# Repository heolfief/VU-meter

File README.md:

# VU-meter

## Table of contents

- [Description](#description)
- [Hardware](#hardware)
- [Software](#software)
- [Copyright and license](#copyright-and-license)

## Description
This project is an AVR based LED VU-meter. It's display consists of 80 LEDs per audio channel. Each PCB holds all the LEDs, the analog and digital segments of the circuit and only handle one audio channel. That way you can build a stereo VU-meter just by using two instances of this circuit (which can be mechanically stacked together). Each audio channel will be completely separated and computed separately by the AVR microcontroller on each PCB.

### Pictures

## Hardware
The hardware is based on 3 main components:
- ATmega328p AVR microcontroller
- MCP6004 quad op-amp
- 74HC595 shift-registers for extended MCU outputs

This board runs on 5V DC power and should not exceed 500mA of current draw (All LEDs lit up).
A stabilized power supply is needed in order to provide clean power to the analog circuit.

### PCB
Populated PCB picture:

Bare PCB pictures:

The PCB was manufactured by <a target="_blank" href="https://www.pcbway.com">PCBWay</a>. Total cost was 44$ including shipping to France by DHL for 5 pieces.

I received the PCB 6 days after placing order on their website. General quality is good. Highly recommend their service.

### Documents available

- <a target="_blank" href="https://github.com/heolfief/VU-meter/blob/master/Hardware/Schematics.pdf">Schematics (PDF)</a>
- <a target="_blank" href="https://github.com/heolfief/VU-meter/blob/master/Hardware/BOM.pdf">Bill of materials (PDF)</a>
- <a target="_blank" href="https://github.com/heolfief/VU-meter/blob/master/Hardware/CAD/Eagle%20files">Autodesk Eagle CAD files</a>
- <a href="https://github.com/heolfief/VU-meter/tree/master/Hardware/CAD/GerberFiles">Gerber files</a>

## Software
The Firmware for the AVR microcontroller is written in C.

- IDE : Atmel Studio 7.0 (can be opened in MPLAB X)
- Compiler : avr-gcc

### Documents available

- <a target="_blank" href="https://heolfief.github.io/VU-meter/">Code documentation (doxygen)</a>

## Copyright and license
heolfief/VU-meter is licensed under the GNU General Public License v3.0.

See the <a target="_blank" href="https://github.com/heolfief/VU-meter/blob/master/LICENSE">LICENSE file</a> for more information.

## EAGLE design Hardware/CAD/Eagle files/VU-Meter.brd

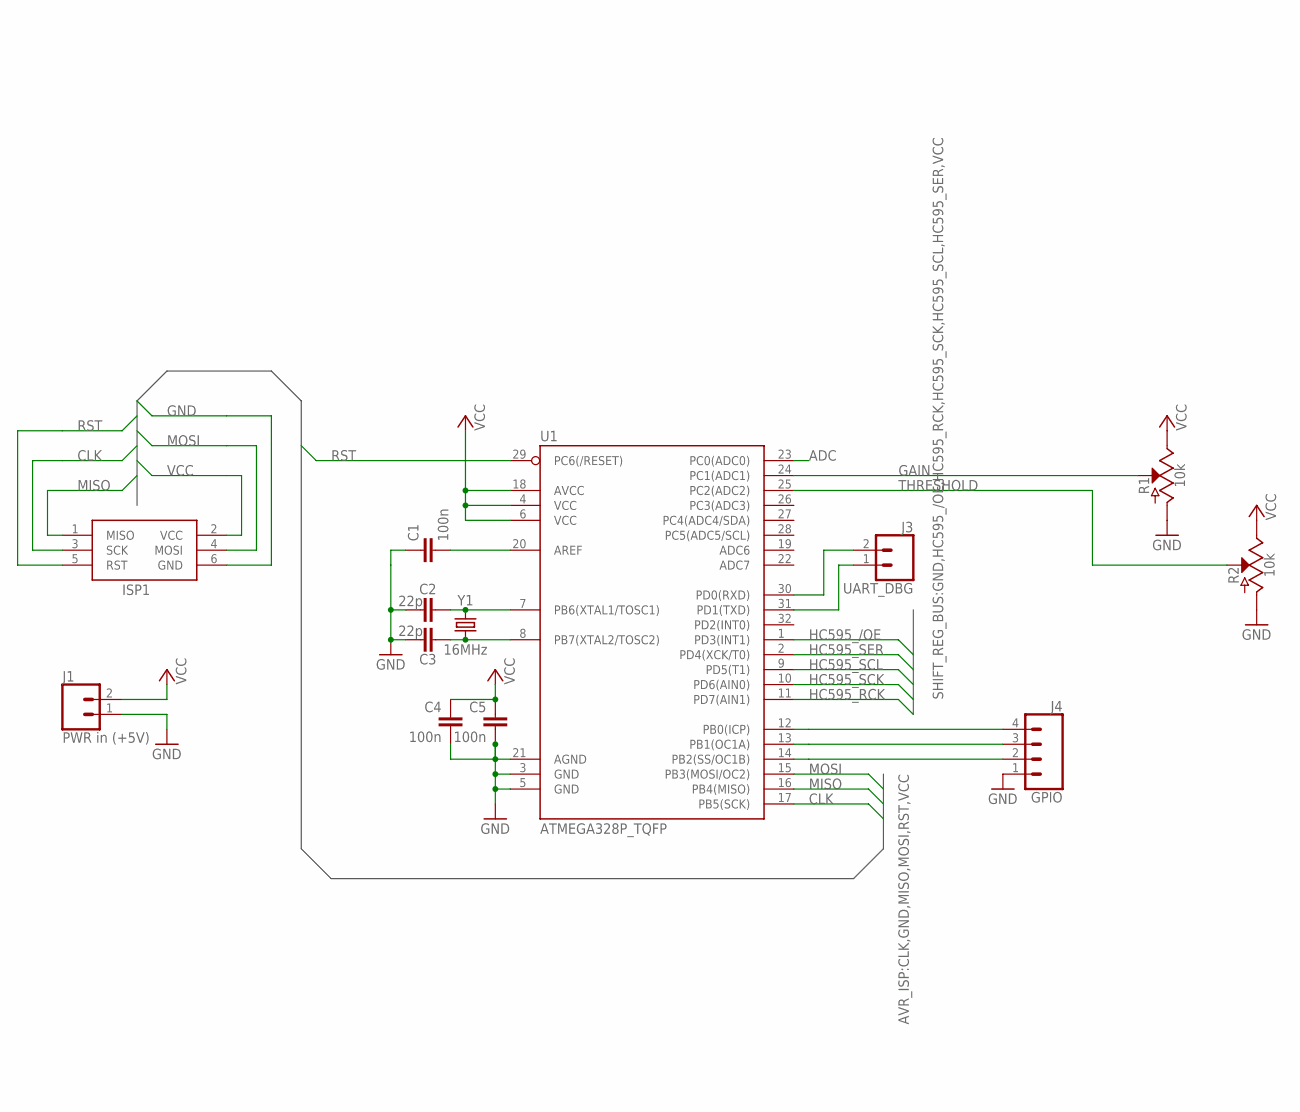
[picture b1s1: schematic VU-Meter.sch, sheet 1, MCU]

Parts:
C1, C4, C5: 100n; C0805
C2, C3: 22p; C0805
ISP1: AVRISP-6; AVRISP
J1: PWR in (+5V); 1X02
J3: UART_DBG; 1X02
J4: GPIO; 1X04
R1, R2: 10k; 1X03
U1: ATMEGA328P_TQFP; TQFP32-08
Y1: 16MHz; CRYSTAL-SMD-3.2X2.5MM

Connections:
ADC: U1.23 (PC0(ADC0)); also elsewhere on the board
CLK: ISP1.3 (SCK), U1.17 (PB5(SCK))
GAIN: R1.2 (S), U1.24 (PC1(ADC1))
GND: C1.1, C2.1, C3.1, C4.2, C5.2, ISP1.6 (GND), J1.1, J4.1, R1.3 (A), R2.3 (A), U1.3 (GND), U1.5 (GND), U1.21 (AGND); also elsewhere on the board
HC595_/OE: U1.1 (PD3(INT1)); also elsewhere on the board
HC595_RCK: U1.11 (PD7(AIN1)); also elsewhere on the board
HC595_SCK: U1.10 (PD6(AIN0)); also elsewhere on the board
HC595_SCL: U1.9 (PD5(T1)); also elsewhere on the board
HC595_SER: U1.2 (PD4(XCK/T0)); also elsewhere on the board
MISO: ISP1.1 (MISO), U1.16 (PB4(MISO))
MOSI: ISP1.4 (MOSI), U1.15 (PB3(MOSI/OC2))
unnamed: C1.2, U1.20 (AREF)
unnamed: C2.2, U1.7 (PB6(XTAL1/TOSC1)), Y1.3 (2)
unnamed: C3.2, U1.8 (PB7(XTAL2/TOSC2)), Y1.1
unnamed: J3.2, U1.30 (PD0(RXD))
unnamed: J3.1, U1.31 (PD1(TXD))
unnamed: J4.4, U1.12 (PB0(ICP))
unnamed: J4.3, U1.13 (PB1(OC1A))
unnamed: J4.2, U1.14 (PB2(SS/OC1B))
RST: ISP1.5 (RST), U1.29 (PC6(/RESET))
THRESHOLD: R2.2 (S), U1.25 (PC2(ADC2))
VCC: C4.1, C5.1, ISP1.2 (VCC), J1.2, R1.1 (E), R2.1 (E), U1.4 (VCC), U1.6 (VCC), U1.18 (AVCC); also elsewhere on the board

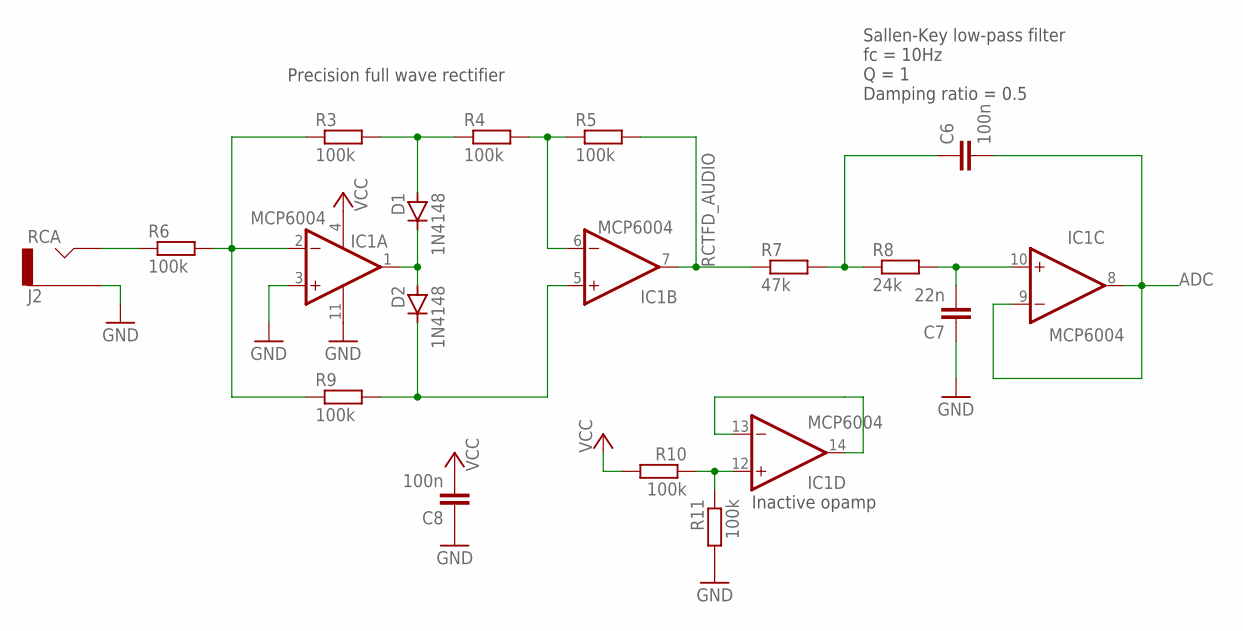
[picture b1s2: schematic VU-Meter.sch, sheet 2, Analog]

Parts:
C6, C8: 100n; C0805
C7: 22n; C0805
D1, D2: 1N4148; SOD80
IC1: MCP6004; SO14
J2: RCA; 1X02
R3, R4, R5, R6, R9, R10, R11: 100k; R0805
R7: 47k; R0805
R8: 24k; R0805

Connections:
ADC: C6.2, IC1.8 (OUT), IC1.9 (-IN); also elsewhere on the board
GND: C7.1, C8.1, IC1.3 (+IN), IC1.11 (V-), J2.2 (SLEEVE), R11.2; also elsewhere on the board
unnamed: IC1.2 (-IN), R3.1, R6.2, R9.1
unnamed: D2.1 (C), IC1.5 (+IN), R9.2
unnamed: D1.1 (C), D2.2 (A), IC1.1 (OUT)
unnamed: D1.2 (A), R3.2, R4.1
unnamed: IC1.6 (-IN), R4.2, R5.1
unnamed: J2.1 (TIP), R6.1
unnamed: C6.1, R7.2, R8.1
unnamed: C7.2, IC1.10 (+IN), R8.2
unnamed: IC1.13 (-IN), IC1.14 (OUT)
unnamed: IC1.12 (+IN), R10.1, R11.1
RCTFD_AUDIO: IC1.7 (OUT), R5.2, R7.1
VCC: C8.2, IC1.4 (V+), R10.2; also elsewhere on the board

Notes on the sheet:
Precision full wave rectifier
Sallen-Key low-pass filter fc = 10Hz Q = 1 Damping ratio = 0.5
Inactive opamp

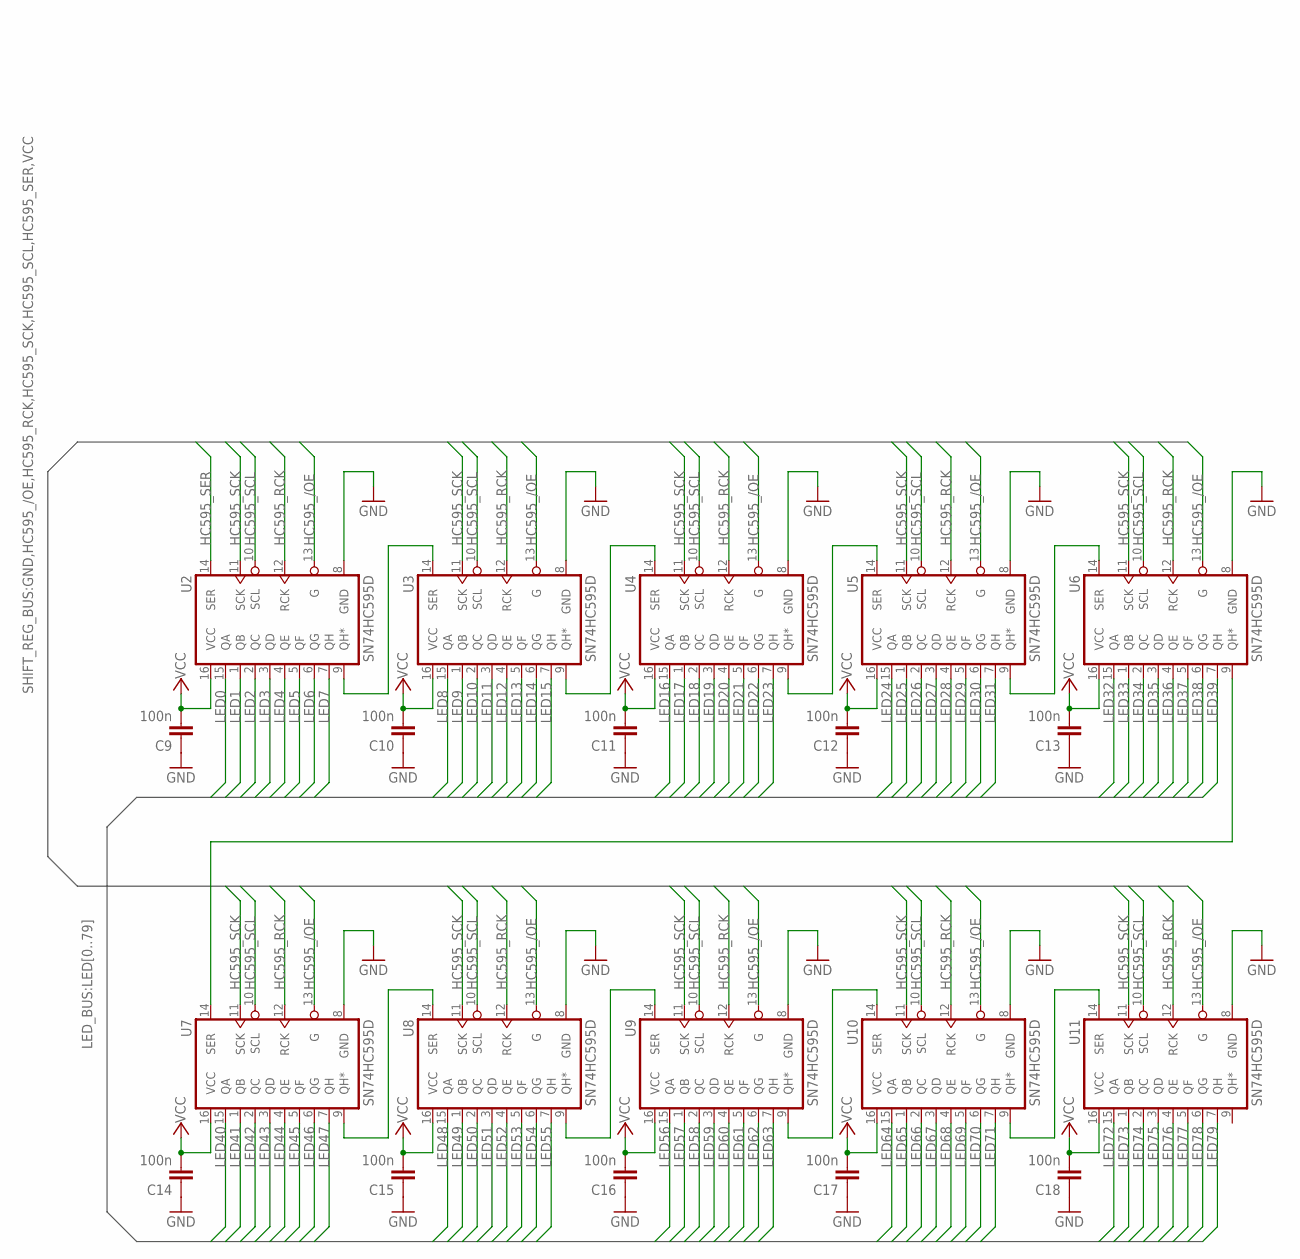
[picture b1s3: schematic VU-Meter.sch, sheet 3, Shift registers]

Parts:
C9, C10, C11, C12, C13, C14, C15, C16, C17, C18: 100n; C0805
U2, U3, U4, U5, U6, U7, U8, U9, U10, U11: SN74HC595D; SO16

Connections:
GND: C9.1, C10.1, C11.1, C12.1, C13.1, C14.1, C15.1, C16.1, C17.1, C18.1, U2.8 (GND), U3.8 (GND), U4.8 (GND), U5.8 (GND), U6.8 (GND), U7.8 (GND), U8.8 (GND), U9.8 (GND), U10.8 (GND), U11.8 (GND); also elsewhere on the board
HC595_/OE: U2.13 (G), U3.13 (G), U4.13 (G), U5.13 (G), U6.13 (G), U7.13 (G), U8.13 (G), U9.13 (G), U10.13 (G), U11.13 (G); also elsewhere on the board
HC595_RCK: U2.12 (RCK), U3.12 (RCK), U4.12 (RCK), U5.12 (RCK), U6.12 (RCK), U7.12 (RCK), U8.12 (RCK), U9.12 (RCK), U10.12 (RCK), U11.12 (RCK); also elsewhere on the board
HC595_SCK: U2.11 (SCK), U3.11 (SCK), U4.11 (SCK), U5.11 (SCK), U6.11 (SCK), U7.11 (SCK), U8.11 (SCK), U9.11 (SCK), U10.11 (SCK), U11.11 (SCK); also elsewhere on the board
HC595_SCL: U2.10 (SCL), U3.10 (SCL), U4.10 (SCL), U5.10 (SCL), U6.10 (SCL), U7.10 (SCL), U8.10 (SCL), U9.10 (SCL), U10.10 (SCL), U11.10 (SCL); also elsewhere on the board
HC595_SER: U2.14 (SER); also elsewhere on the board
LED0: U2.15 (QA); also elsewhere on the board
LED1: U2.1 (QB); also elsewhere on the board
LED2: U2.2 (QC); also elsewhere on the board
LED3: U2.3 (QD); also elsewhere on the board
LED4: U2.4 (QE); also elsewhere on the board
LED5: U2.5 (QF); also elsewhere on the board
LED6: U2.6 (QG); also elsewhere on the board
LED7: U2.7 (QH); also elsewhere on the board
LED8: U3.15 (QA); also elsewhere on the board
LED9: U3.1 (QB); also elsewhere on the board
LED10: U3.2 (QC); also elsewhere on the board
LED11: U3.3 (QD); also elsewhere on the board
LED12: U3.4 (QE); also elsewhere on the board
LED13: U3.5 (QF); also elsewhere on the board
LED14: U3.6 (QG); also elsewhere on the board
LED15: U3.7 (QH); also elsewhere on the board
LED16: U4.15 (QA); also elsewhere on the board
LED17: U4.1 (QB); also elsewhere on the board
LED18: U4.2 (QC); also elsewhere on the board
LED19: U4.3 (QD); also elsewhere on the board
LED20: U4.4 (QE); also elsewhere on the board
LED21: U4.5 (QF); also elsewhere on the board
LED22: U4.6 (QG); also elsewhere on the board
LED23: U4.7 (QH); also elsewhere on the board
LED24: U5.15 (QA); also elsewhere on the board
LED25: U5.1 (QB); also elsewhere on the board
LED26: U5.2 (QC); also elsewhere on the board
LED27: U5.3 (QD); also elsewhere on the board
LED28: U5.4 (QE); also elsewhere on the board
LED29: U5.5 (QF); also elsewhere on the board
LED30: U5.6 (QG); also elsewhere on the board
LED31: U5.7 (QH); also elsewhere on the board
LED32: U6.15 (QA); also elsewhere on the board
LED33: U6.1 (QB); also elsewhere on the board
LED34: U6.2 (QC); also elsewhere on the board
LED35: U6.3 (QD); also elsewhere on the board
LED36: U6.4 (QE); also elsewhere on the board
LED37: U6.5 (QF); also elsewhere on the board
LED38: U6.6 (QG); also elsewhere on the board
LED39: U6.7 (QH); also elsewhere on the board
LED40: U7.15 (QA); also elsewhere on the board
LED41: U7.1 (QB); also elsewhere on the board
LED42: U7.2 (QC); also elsewhere on the board
LED43: U7.3 (QD); also elsewhere on the board
LED44: U7.4 (QE); also elsewhere on the board
LED45: U7.5 (QF); also elsewhere on the board
LED46: U7.6 (QG); also elsewhere on the board
LED47: U7.7 (QH); also elsewhere on the board
LED48: U8.15 (QA); also elsewhere on the board
LED49: U8.1 (QB); also elsewhere on the board
LED50: U8.2 (QC); also elsewhere on the board
LED51: U8.3 (QD); also elsewhere on the board
LED52: U8.4 (QE); also elsewhere on the board
LED53: U8.5 (QF); also elsewhere on the board
LED54: U8.6 (QG); also elsewhere on the board
LED55: U8.7 (QH); also elsewhere on the board
LED56: U9.15 (QA); also elsewhere on the board
LED57: U9.1 (QB); also elsewhere on the board
LED58: U9.2 (QC); also elsewhere on the board
LED59: U9.3 (QD); also elsewhere on the board
LED60: U9.4 (QE); also elsewhere on the board
LED61: U9.5 (QF); also elsewhere on the board
LED62: U9.6 (QG); also elsewhere on the board
LED63: U9.7 (QH); also elsewhere on the board
LED64: U10.15 (QA); also elsewhere on the board
LED65: U10.1 (QB); also elsewhere on the board
LED66: U10.2 (QC); also elsewhere on the board
LED67: U10.3 (QD); also elsewhere on the board
LED68: U10.4 (QE); also elsewhere on the board
LED69: U10.5 (QF); also elsewhere on the board
LED70: U10.6 (QG); also elsewhere on the board
LED71: U10.7 (QH); also elsewhere on the board
LED72: U11.15 (QA); also elsewhere on the board
LED73: U11.1 (QB); also elsewhere on the board
LED74: U11.2 (QC); also elsewhere on the board
LED75: U11.3 (QD); also elsewhere on the board
LED76: U11.4 (QE); also elsewhere on the board
LED77: U11.5 (QF); also elsewhere on the board
LED78: U11.6 (QG); also elsewhere on the board
LED79: U11.7 (QH); also elsewhere on the board
unnamed: U2.9 (QH*), U3.14 (SER)
unnamed: U3.9 (QH*), U4.14 (SER)
unnamed: U4.9 (QH*), U5.14 (SER)
unnamed: U5.9 (QH*), U6.14 (SER)
unnamed: U7.9 (QH*), U8.14 (SER)
unnamed: U8.9 (QH*), U9.14 (SER)
unnamed: U9.9 (QH*), U10.14 (SER)
unnamed: U10.9 (QH*), U11.14 (SER)
unnamed: U6.9 (QH*), U7.14 (SER)
VCC: C9.2, C10.2, C11.2, C12.2, C13.2, C14.2, C15.2, C16.2, C17.2, C18.2, U2.16 (VCC), U3.16 (VCC), U4.16 (VCC), U5.16 (VCC), U6.16 (VCC), U7.16 (VCC), U8.16 (VCC), U9.16 (VCC), U10.16 (VCC), U11.16 (VCC); also elsewhere on the board

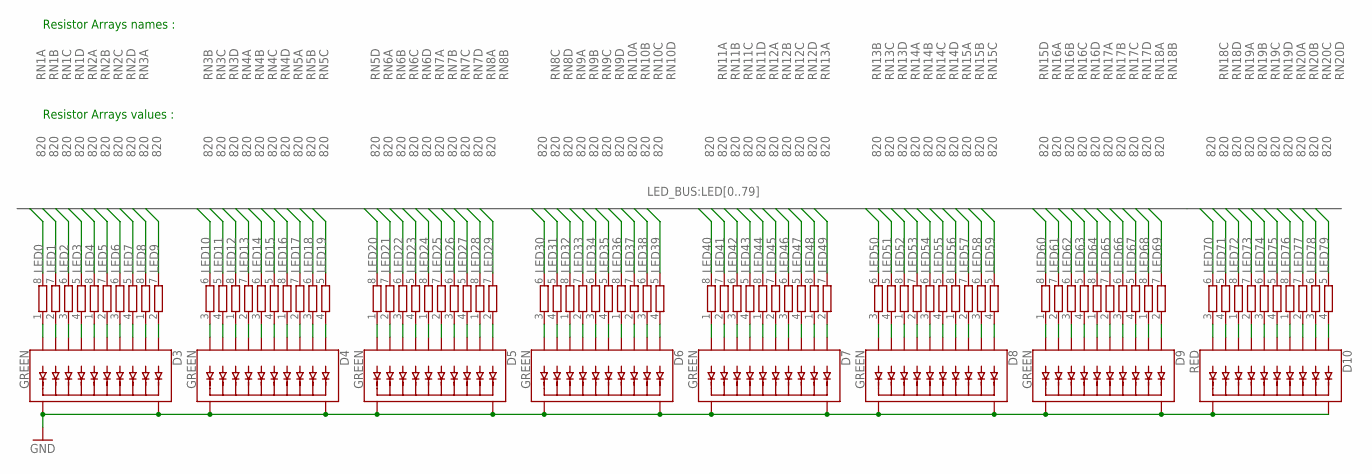
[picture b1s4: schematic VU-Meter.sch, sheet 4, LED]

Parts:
D3, D4, D5, D6, D7, D8, D9: GREEN; LED_BARGRAPH_OFFBOARD_RIGHT_ANGLE
D10: RED; LED_BARGRAPH_OFFBOARD_RIGHT_ANGLE
RN1, RN2, RN3, RN4, RN5, RN6, RN7, RN8, RN9, RN10, RN11, RN12, RN13, RN14, RN15, RN16, RN17, RN18, RN19, RN20: 820; 0603-ARC

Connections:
GND: D3.P$11 (C), D3.P$12 (C1), D4.P$11 (C), D4.P$12 (C1), D5.P$11 (C), D5.P$12 (C1), D6.P$11 (C), D6.P$12 (C1), D7.P$11 (C), D7.P$12 (C1), D8.P$11 (C), D8.P$12 (C1), D9.P$11 (C), D9.P$12 (C1), D10.P$11 (C), D10.P$12 (C1); also elsewhere on the board
LED0: RN1.8 (2); also elsewhere on the board
LED1: RN1.7 (2); also elsewhere on the board
LED2: RN1.6 (2); also elsewhere on the board
LED3: RN1.5 (2); also elsewhere on the board
LED4: RN2.8 (2); also elsewhere on the board
LED5: RN2.7 (2); also elsewhere on the board
LED6: RN2.6 (2); also elsewhere on the board
LED7: RN2.5 (2); also elsewhere on the board
LED8: RN3.8 (2); also elsewhere on the board
LED9: RN3.7 (2); also elsewhere on the board
LED10: RN3.6 (2); also elsewhere on the board
LED11: RN3.5 (2); also elsewhere on the board
LED12: RN4.8 (2); also elsewhere on the board
LED13: RN4.7 (2); also elsewhere on the board
LED14: RN4.6 (2); also elsewhere on the board
LED15: RN4.5 (2); also elsewhere on the board
LED16: RN5.8 (2); also elsewhere on the board
LED17: RN5.7 (2); also elsewhere on the board
LED18: RN5.6 (2); also elsewhere on the board
LED19: RN5.5 (2); also elsewhere on the board
LED20: RN6.8 (2); also elsewhere on the board
LED21: RN6.7 (2); also elsewhere on the board
LED22: RN6.6 (2); also elsewhere on the board
LED23: RN6.5 (2); also elsewhere on the board
LED24: RN7.8 (2); also elsewhere on the board
LED25: RN7.7 (2); also elsewhere on the board
LED26: RN7.6 (2); also elsewhere on the board
LED27: RN7.5 (2); also elsewhere on the board
LED28: RN8.8 (2); also elsewhere on the board
LED29: RN8.7 (2); also elsewhere on the board
LED30: RN8.6 (2); also elsewhere on the board
LED31: RN8.5 (2); also elsewhere on the board
LED32: RN9.8 (2); also elsewhere on the board
LED33: RN9.7 (2); also elsewhere on the board
LED34: RN9.6 (2); also elsewhere on the board
LED35: RN9.5 (2); also elsewhere on the board
LED36: RN10.8 (2); also elsewhere on the board
LED37: RN10.7 (2); also elsewhere on the board
LED38: RN10.6 (2); also elsewhere on the board
LED39: RN10.5 (2); also elsewhere on the board
LED40: RN11.8 (2); also elsewhere on the board
LED41: RN11.7 (2); also elsewhere on the board
LED42: RN11.6 (2); also elsewhere on the board
LED43: RN11.5 (2); also elsewhere on the board
LED44: RN12.8 (2); also elsewhere on the board
LED45: RN12.7 (2); also elsewhere on the board
LED46: RN12.6 (2); also elsewhere on the board
LED47: RN12.5 (2); also elsewhere on the board
LED48: RN13.8 (2); also elsewhere on the board
LED49: RN13.7 (2); also elsewhere on the board
LED50: RN13.6 (2); also elsewhere on the board
LED51: RN13.5 (2); also elsewhere on the board
LED52: RN14.8 (2); also elsewhere on the board
LED53: RN14.7 (2); also elsewhere on the board
LED54: RN14.6 (2); also elsewhere on the board
LED55: RN14.5 (2); also elsewhere on the board
LED56: RN15.8 (2); also elsewhere on the board
LED57: RN15.7 (2); also elsewhere on the board
LED58: RN15.6 (2); also elsewhere on the board
LED59: RN15.5 (2); also elsewhere on the board
LED60: RN16.8 (2); also elsewhere on the board
LED61: RN16.7 (2); also elsewhere on the board
LED62: RN16.6 (2); also elsewhere on the board
LED63: RN16.5 (2); also elsewhere on the board
LED64: RN17.8 (2); also elsewhere on the board
LED65: RN17.7 (2); also elsewhere on the board
LED66: RN17.6 (2); also elsewhere on the board
LED67: RN17.5 (2); also elsewhere on the board
LED68: RN18.8 (2); also elsewhere on the board
LED69: RN18.7 (2); also elsewhere on the board
LED70: RN18.6 (2); also elsewhere on the board
LED71: RN18.5 (2); also elsewhere on the board
LED72: RN19.8 (2); also elsewhere on the board
LED73: RN19.7 (2); also elsewhere on the board
LED74: RN19.6 (2); also elsewhere on the board
LED75: RN19.5 (2); also elsewhere on the board
LED76: RN20.8 (2); also elsewhere on the board
LED77: RN20.7 (2); also elsewhere on the board
LED78: RN20.6 (2); also elsewhere on the board
LED79: RN20.5 (2); also elsewhere on the board
unnamed: D3.P$1 (A9), RN1.1
unnamed: D3.P$2 (A8), RN1.2 (1)
unnamed: D3.P$3 (A7), RN1.3 (1)
unnamed: D3.P$4 (A6), RN1.4 (1)
unnamed: D3.P$5 (A5), RN2.1
unnamed: D3.P$6 (A4), RN2.2 (1)
unnamed: D3.P$7 (A3), RN2.3 (1)
unnamed: D3.P$8 (A2), RN2.4 (1)
unnamed: D3.P$9 (A1), RN3.1
unnamed: D3.P$10 (A), RN3.2 (1)
unnamed: D4.P$1 (A9), RN3.3 (1)
unnamed: D4.P$2 (A8), RN3.4 (1)
unnamed: D4.P$3 (A7), RN4.1
unnamed: D4.P$4 (A6), RN4.2 (1)
unnamed: D4.P$5 (A5), RN4.3 (1)
unnamed: D4.P$6 (A4), RN4.4 (1)
unnamed: D4.P$7 (A3), RN5.1
unnamed: D4.P$8 (A2), RN5.2 (1)
unnamed: D4.P$9 (A1), RN5.3 (1)
unnamed: D4.P$10 (A), RN5.4 (1)
unnamed: D5.P$1 (A9), RN6.1
unnamed: D5.P$2 (A8), RN6.2 (1)
unnamed: D5.P$3 (A7), RN6.3 (1)
unnamed: D5.P$4 (A6), RN6.4 (1)
unnamed: D5.P$5 (A5), RN7.1
unnamed: D5.P$6 (A4), RN7.2 (1)
unnamed: D5.P$7 (A3), RN7.3 (1)
unnamed: D5.P$8 (A2), RN7.4 (1)
unnamed: D5.P$9 (A1), RN8.1
unnamed: D5.P$10 (A), RN8.2 (1)
unnamed: D6.P$1 (A9), RN8.3 (1)
unnamed: D6.P$2 (A8), RN8.4 (1)
unnamed: D6.P$3 (A7), RN9.1
unnamed: D6.P$4 (A6), RN9.2 (1)
unnamed: D6.P$5 (A5), RN9.3 (1)
unnamed: D6.P$6 (A4), RN9.4 (1)
unnamed: D6.P$7 (A3), RN10.1
unnamed: D6.P$8 (A2), RN10.2 (1)
unnamed: D6.P$9 (A1), RN10.3 (1)
unnamed: D6.P$10 (A), RN10.4 (1)
unnamed: D7.P$1 (A9), RN11.1
unnamed: D7.P$2 (A8), RN11.2 (1)
unnamed: D7.P$3 (A7), RN11.3 (1)
unnamed: D7.P$4 (A6), RN11.4 (1)
unnamed: D7.P$5 (A5), RN12.1
unnamed: D7.P$6 (A4), RN12.2 (1)
unnamed: D7.P$7 (A3), RN12.3 (1)
unnamed: D7.P$8 (A2), RN12.4 (1)
unnamed: D7.P$9 (A1), RN13.1
unnamed: D7.P$10 (A), RN13.2 (1)
unnamed: D8.P$1 (A9), RN13.3 (1)
unnamed: D8.P$2 (A8), RN13.4 (1)
unnamed: D8.P$3 (A7), RN14.1
unnamed: D8.P$4 (A6), RN14.2 (1)
unnamed: D8.P$5 (A5), RN14.3 (1)
unnamed: D8.P$6 (A4), RN14.4 (1)
unnamed: D8.P$7 (A3), RN15.1
unnamed: D8.P$8 (A2), RN15.2 (1)
unnamed: D8.P$9 (A1), RN15.3 (1)
unnamed: D8.P$10 (A), RN15.4 (1)
unnamed: D9.P$1 (A9), RN16.1
unnamed: D9.P$2 (A8), RN16.2 (1)
unnamed: D9.P$3 (A7), RN16.3 (1)
unnamed: D9.P$4 (A6), RN16.4 (1)
unnamed: D9.P$5 (A5), RN17.1
unnamed: D9.P$6 (A4), RN17.2 (1)
unnamed: D9.P$7 (A3), RN17.3 (1)
unnamed: D9.P$8 (A2), RN17.4 (1)
unnamed: D9.P$9 (A1), RN18.1
unnamed: D9.P$10 (A), RN18.2 (1)
unnamed: D10.P$1 (A9), RN18.3 (1)
unnamed: D10.P$2 (A8), RN18.4 (1)
unnamed: D10.P$3 (A7), RN19.1
unnamed: D10.P$4 (A6), RN19.2 (1)
unnamed: D10.P$5 (A5), RN19.3 (1)
unnamed: D10.P$6 (A4), RN19.4 (1)
unnamed: D10.P$7 (A3), RN20.1
unnamed: D10.P$8 (A2), RN20.2 (1)
unnamed: D10.P$9 (A1), RN20.3 (1)
unnamed: D10.P$10 (A), RN20.4 (1)

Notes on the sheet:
Resistor Arrays names :
Resistor Arrays values :

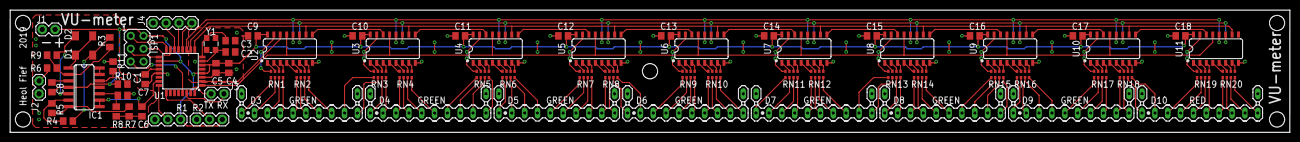
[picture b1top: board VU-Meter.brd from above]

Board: 2 copper layers, 252.7 x 24.1 mm, 77 parts (0 on the bottom side), 202 nets.

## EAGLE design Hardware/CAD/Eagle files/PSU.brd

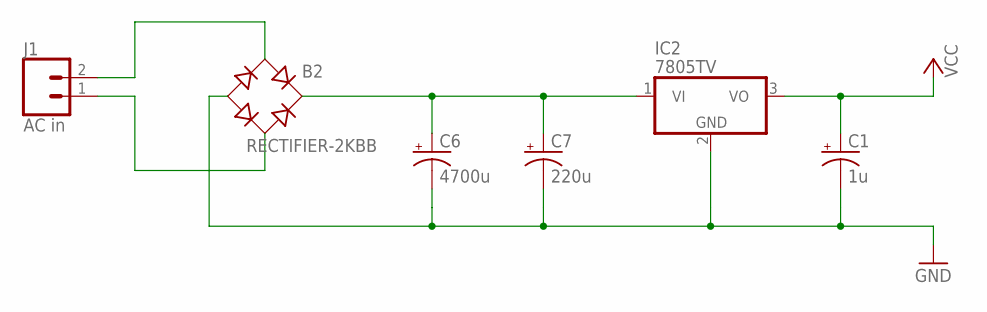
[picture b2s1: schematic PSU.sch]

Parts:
B2: RECTIFIER-2KBB; 2KBB
C1: 1u; E2,5-5
C6: 4700u; E7,5-16
C7: 220u; E2,5-6
IC2: 7805TV; TO220V
J1: AC in; 1X02

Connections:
GND: B2.-, C1.-, C6.-, C7.-, IC2.2 (GND)
unnamed: B2.AC1, J1.2
unnamed: B2.AC2, J1.1
unnamed: B2.+, C6.+, C7.+, IC2.1 (VI)
VCC: C1.+, IC2.3 (VO)

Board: 2 copper layers, 6 parts (0 on the bottom side), 5 nets, no tracks yet.

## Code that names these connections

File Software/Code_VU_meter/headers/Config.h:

/*
 * Config.h
 *
 * Created: 30/10/2018 23:15:32
 *  Author: Heol Fief
 */ 


#ifndef CONFIG_H_
#define CONFIG_H_

/* SOFTWARE CONFIG */
#define AVERAGEWIDTH			4			// Number of samples for the digital filter
#define PEAK_HOLD_TIME			600			// Hold time for the peak before falling
#define PEAK_FALL_RATE			0.2			// Speed for the peak to fall

#define GAIN_MIN				0.5			// Minimal input signal gain
#define GAIN_MAX				2.0			// Maximal input signal gain

/* HARDWARE CONFIG */
#define NUMBER_OF_LED			80			// Number of LED for the VU meter display

#define AUDIO_ADC_CHANNEL		0			// ADC channel to read audio signal from
#define GAIN_ADC_CHANNEL		1			// ADC channel to read gain from
#define THRESHOLD_ADC_CHANNEL	2			// ADC channel to read threshold from

#define HC595_PORT				PORTD		// IO port where HC595 is connected
#define HC595_DDR				DDRD		// DATA DIRECTION REGISTER of the port chosen above

#define HC595_SER				PD7		    // Data pin (DS) pin location
#define HC595_SCK				PD5			// Shift Clock (SH_CP) pin location
#define HC595_RCK				PD4			// Register Clock (SH_CP) pin location
#define HC595_SCL				PD6			// Serial clear (active LOW) pin location
#define HC595_OE				PD3			// Output Enable (active LOW) pin location

#endif /* CONFIG_H_ */

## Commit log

2018-10-30 Update gitignore
2018-10-30 Rename gitignore to .gitignore
2018-11-06 initial release
2019-01-17 Create newfolder
2019-01-17 [ImgBot] Optimize images
    *Total -- 194.12kb -> 161.51kb (16.8%)
    /Software/Doxygen_code_doc/html/doxygen.png -- 3.69kb -> 2.50kb (32.26%)
    /Software/Doxygen_code_doc/html/_h_c595_8h__incl.png -- 2.21kb -> 1.71kb (22.6%)
    /Software/Doxygen_code_doc/html/wdt_8h__dep__incl.png -- 3.68kb -> 3.02kb (17.76%)
    /Software/Doxygen_code_doc/html/_peripherals_8c__incl.png -- 17.46kb -> 14.37kb (17.69%)
    /Software/Doxygen_code_doc/html/search/mag_sel.png -- 0.55kb -> 0.45kb (17.41%)
2019-01-19 Create CNAME
2019-03-29 Initial release
    Initial release
    Initial release
    Initial release
    Create Enclosure Mechanical Drawing.pdf
    Add pcb prictures
    Update README.md
2019-03-29 [ImgBot] Optimize images
    *Total -- 1,769.57kb -> 1,682.04kb (4.95%)
    /docs/data__structure_8h__incl.png -- 3.08kb -> 2.05kb (33.32%)
    /docs/doxygen.png -- 3.69kb -> 2.50kb (32.26%)
    /docs/hc595_8h__incl.png -- 2.38kb -> 1.70kb (28.43%)
    /docs/dsp_8h__dep__incl.png -- 1.74kb -> 1.39kb (20%)
    /docs/usart_8h__dep__incl.png -- 6.66kb -> 5.47kb (17.81%)
2019-03-29 Add gitignore
2019-03-29 Add software files
2019-03-29 Add hardware files
2019-03-29 Add doxygen doc to github pages
2019-06-27 Add images
2019-06-27 Reduce image size
2019-06-27 Rotate image
2019-06-27 [ImgBot] Optimize images
    *Total -- 6,159.02kb -> 5,913.80kb (3.98%)
    /docs/img/_MG_8804-Modifier.jpg -- 732.44kb -> 684.50kb (6.54%)
    /docs/img/_MG_8807-Modifier.jpg -- 380.85kb -> 358.41kb (5.89%)
    /docs/img/_MG_8805-Modifier.jpg -- 874.58kb -> 823.58kb (5.83%)
    /docs/img/_MG_8800-Modifier.jpg -- 482.73kb -> 455.96kb (5.55%)
    /docs/img/_MG_8809-Modifier.jpg -- 482.62kb -> 460.55kb (4.57%)
2019-06-27 crop images
2019-06-27 Add leds

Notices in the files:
parts and their libraries:
SparkFun-Connectors: Licensing: Creative Commons ShareAlike 4.0 International - https://creativecommons.org/licenses/by-sa/4.0
